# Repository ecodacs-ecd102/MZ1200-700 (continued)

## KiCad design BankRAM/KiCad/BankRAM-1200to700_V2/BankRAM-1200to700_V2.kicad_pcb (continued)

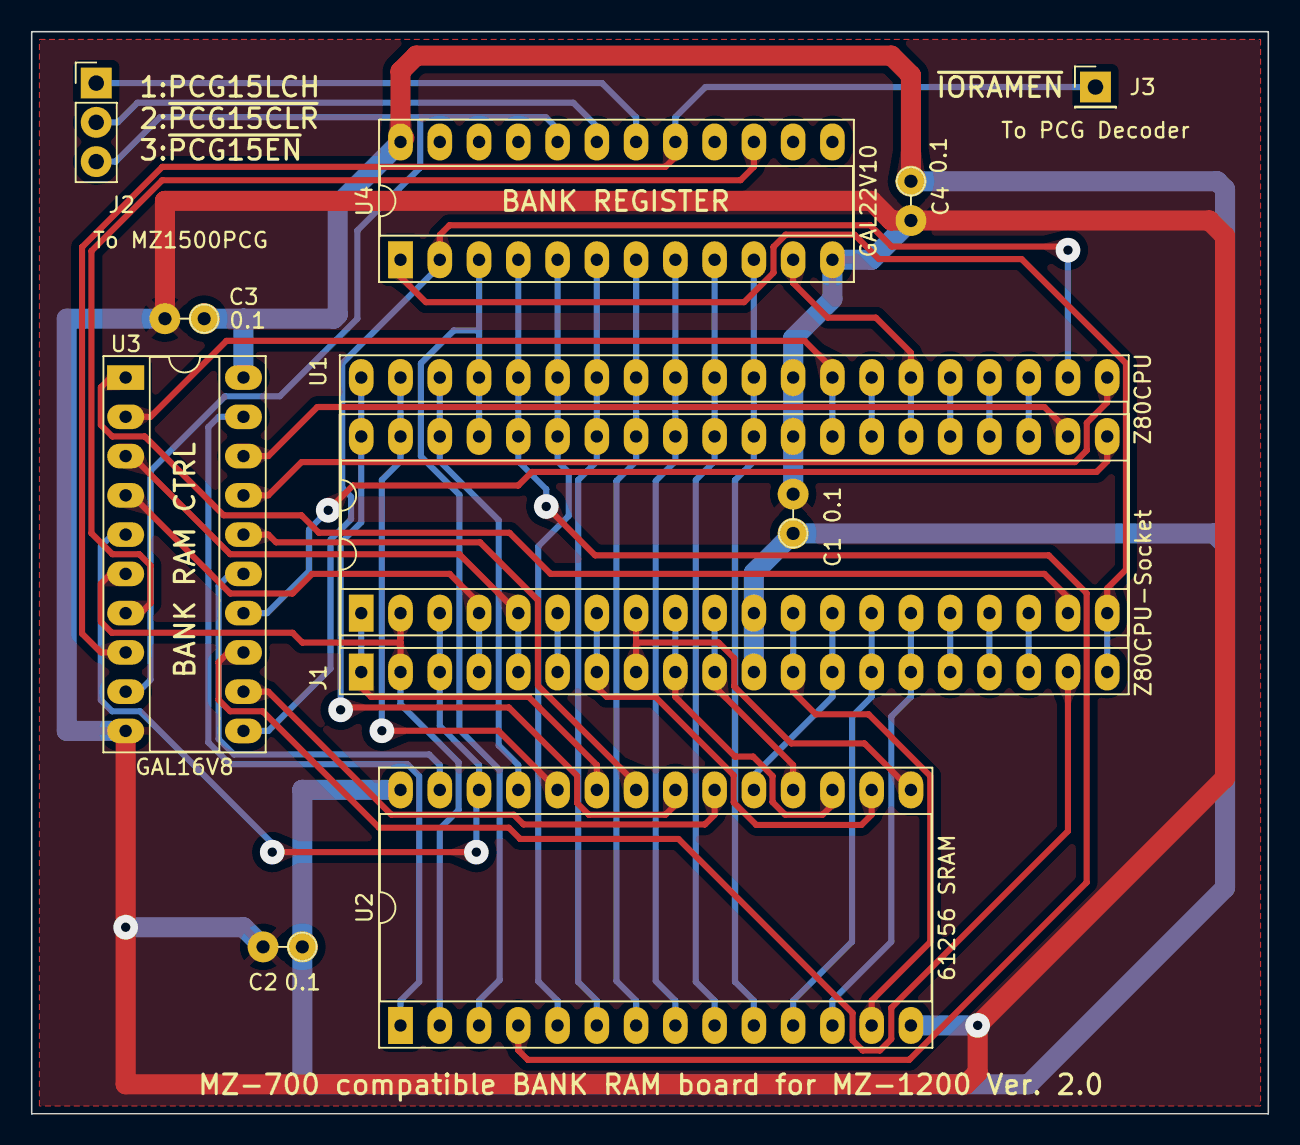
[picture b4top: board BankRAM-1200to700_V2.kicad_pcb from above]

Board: 2 copper layers, 80.0 x 70.0 mm, 11 parts (0 on the bottom side), 52 nets.

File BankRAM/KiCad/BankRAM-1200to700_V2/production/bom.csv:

Designator,Footprint,Quantity,Value,LCSC Part #
"C1, C2, C3, C4",LargePad_R_Axial_DIN0204_L3.6mm_D1.6mm_P2.54mm_Vertical,4,0.1,
J1,DIP-40_W15.24mm_Socket_LongPads,1,Z80CPU-Socket,
J2,PinHeader_1x03_P2.54mm_Vertical,1,To MZ1500PCG,
J3,PinHeader_1x01_P2.54mm_Vertical,1,To PCG Decoder,
U1,DIP-40_W15.24mm_Socket_LongPads,1,Z80CPU,
U2,DIP-28_W15.24mm_Socket_LongPads,1,61256 SRAM,
U3,DIP-20_W7.62mm_Socket_LongPads,1,GAL16V8,
U4,DIP-24_W7.62mm_Socket_LongPads,1,GAL22V10,

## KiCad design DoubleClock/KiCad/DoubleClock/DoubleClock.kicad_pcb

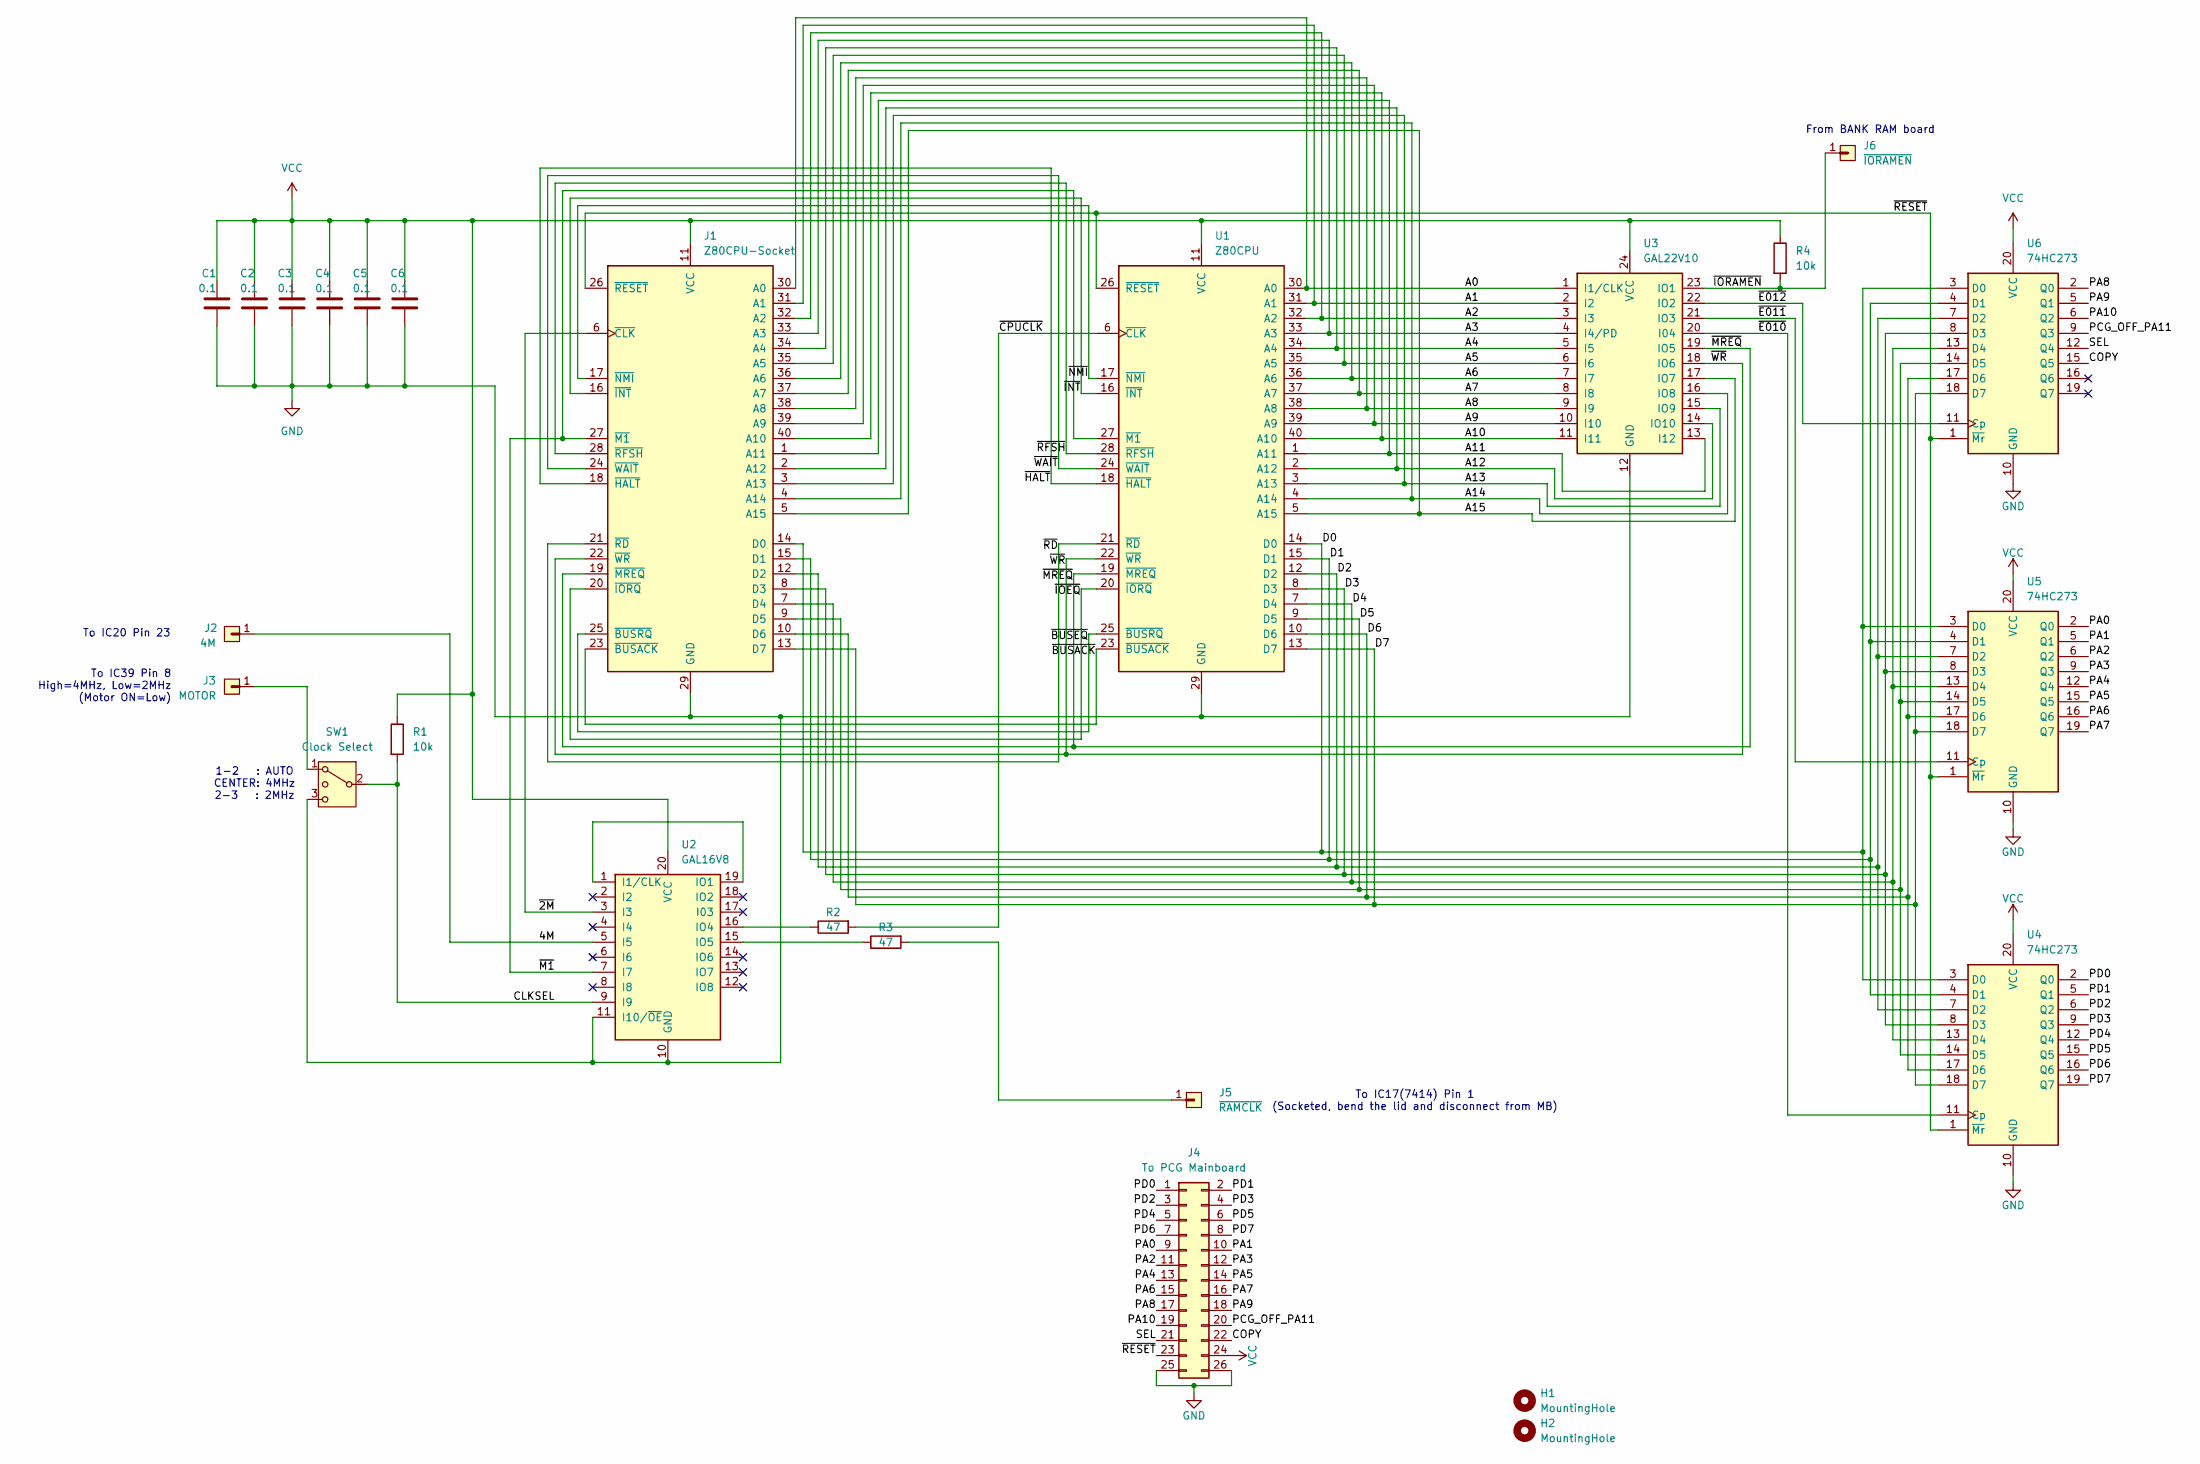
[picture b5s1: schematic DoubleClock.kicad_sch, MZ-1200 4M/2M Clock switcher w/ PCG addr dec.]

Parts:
C1, C2, C3, C4, C5, C6: 0.1; LargePad_R_Axial_DIN0207_L6.3mm_D2.5mm_P7.62mm_Horizontal
H1, H2: MountingHole; MountingHole_3.2mm_M3
J1: Z80CPU-Socket; DIP-40_W15.24mm_Socket_LongPads
J2: 4M; PinHeader_1x01_P2.54mm_Vertical
J3: MOTOR; PinHeader_1x01_P2.54mm_Vertical
J4: To PCG Mainboard; PinSocket_2x13_P2.54mm_Vertical_LargePad
J5: ~{RAMCLK}; PinHeader_1x01_P2.54mm_Vertical
J6: ~{IORAMEN}; PinHeader_1x01_P2.54mm_Vertical
R1, R4: 10k; LargePad_R_Axial_DIN0204_L3.6mm_D1.6mm_P2.54mm_Vertical
R2, R3: 47; LargePad_R_Axial_DIN0204_L3.6mm_D1.6mm_P2.54mm_Vertical
SW1: Clock Select; PinSocket_1x03_P2.54mm_Vertical
U1: Z80CPU; DIP-40_W15.24mm_Socket_LongPads
U2: GAL16V8; DIP-20_W7.62mm_Socket_LongPads
U3: GAL22V10; DIP-24_W7.62mm_Socket_LongPads
U4, U5, U6: 74HC273; DIP-20_W7.62mm_Socket_LongPads

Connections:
/4M: J2.1, U2.5 (I5)
/A0: J1.30 (A0), U1.30 (A0), U3.1 (I1/CLK)
/A1: J1.31 (A1), U1.31 (A1), U3.2 (I2)
/A2: J1.32 (A2), U1.32 (A2), U3.3 (I3)
/A3: J1.33 (A3), U1.33 (A3), U3.4 (I4/PD)
/A4: J1.34 (A4), U1.34 (A4), U3.5 (I5)
/A5: J1.35 (A5), U1.35 (A5), U3.6 (I6)
/A6: J1.36 (A6), U1.36 (A6), U3.7 (I7)
/A7: J1.37 (A7), U1.37 (A7), U3.8 (I8)
/A8: J1.38 (A8), U1.38 (A8), U3.9 (I9)
/A9: J1.39 (A9), U1.39 (A9), U3.10 (I10)
/A10: J1.40 (A10), U1.40 (A10), U3.11 (I11)
/A11: J1.1 (A11), U1.1 (A11), U3.13 (I12)
/A12: J1.2 (A12), U1.2 (A12), U3.14 (IO10)
/A13: J1.3 (A13), U1.3 (A13), U3.15 (IO9)
/A14: J1.4 (A14), U1.4 (A14), U3.16 (IO8)
/A15: J1.5 (A15), U1.5 (A15), U3.17 (IO7)
/CLKSEL: R1.2, SW1.2 (3), U2.9 (I9)
/COPY: J4.22, U6.15 (Q5)
/D0: J1.14 (D0), U1.14 (D0), U4.3 (D0), U5.3 (D0), U6.3 (D0)
/D1: J1.15 (D1), U1.15 (D1), U4.4 (D1), U5.4 (D1), U6.4 (D1)
/D2: J1.12 (D2), U1.12 (D2), U4.7 (D2), U5.7 (D2), U6.7 (D2)
/D3: J1.8 (D3), U1.8 (D3), U4.8 (D3), U5.8 (D3), U6.8 (D3)
/D4: J1.7 (D4), U1.7 (D4), U4.13 (D4), U5.13 (D4), U6.13 (D4)
/D5: J1.9 (D5), U1.9 (D5), U4.14 (D5), U5.14 (D5), U6.14 (D5)
/D6: J1.10 (D6), U1.10 (D6), U4.17 (D6), U5.17 (D6), U6.17 (D6)
/D7: J1.13 (D7), U1.13 (D7), U4.18 (D7), U5.18 (D7), U6.18 (D7)
/PA0: J4.9, U5.2 (Q0)
/PA1: J4.10, U5.5 (Q1)
/PA2: J4.11, U5.6 (Q2)
/PA3: J4.12, U5.9 (Q3)
/PA4: J4.13, U5.12 (Q4)
/PA5: J4.14, U5.15 (Q5)
/PA6: J4.15, U5.16 (Q6)
/PA7: J4.16, U5.19 (Q7)
/PA8: J4.17, U6.2 (Q0)
/PA9: J4.18, U6.5 (Q1)
/PA10: J4.19, U6.6 (Q2)
/PCG_OFF_PA11: J4.20, U6.9 (Q3)
/PD0: J4.1, U4.2 (Q0)
/PD1: J4.2, U4.5 (Q1)
/PD2: J4.3, U4.6 (Q2)
/PD3: J4.4, U4.9 (Q3)
/PD4: J4.5, U4.12 (Q4)
/PD5: J4.6, U4.15 (Q5)
/PD6: J4.7, U4.16 (Q6)
/PD7: J4.8, U4.19 (Q7)
/SEL: J4.21, U6.12 (Q4)
/~2M: J1.6 (~CLK), U2.3 (I3)
/~BUSACK: J1.23 (~BUSACK), U1.23 (~BUSACK)
/~BUSEQ: J1.25 (~BUSRQ), U1.25 (~BUSRQ)
/~CPUCLK: R2.2, U1.6 (~CLK)
/~E010: U3.20 (I04), U4.11 (Cp)
/~E011: U3.21 (IO3), U5.11 (Cp)
/~E012: U3.22 (IO2), U6.11 (Cp)
/~HALT: J1.18 (~HALT), U1.18 (~HALT)
/~INT: J1.16 (~INT), U1.16 (~INT)
/~IOEQ: J1.20 (~IORQ), U1.20 (~IORQ)
/~IORAMEN: J6.1, R4.2, U3.23 (IO1)
/~M1: J1.27 (~M1), U1.27 (~M1), U2.7 (I7)
/~MREQ: J1.19 (~MREQ), U1.19 (~MREQ), U3.19 (IO5)
/~NMI: J1.17 (~NMI), U1.17 (~NMI)
/~RD: J1.21 (~RD), U1.21 (~RD)
/~RESET: J1.26 (~RESET), J4.23, U1.26 (~RESET), U4.1 (~Mr), U5.1 (~Mr), U6.1 (~Mr)
/~RFSH: J1.28 (~RFSH), U1.28 (~RFSH)
/~WAIT: J1.24 (~WAIT), U1.24 (~WAIT)
/~WR: J1.22 (~WR), U1.22 (~WR), U3.18 (IO6)
GND: C1.2, C2.2, C3.2, C4.2, C5.2, C6.2, J1.29 (GND), J4.25, J4.26, SW1.3 (4), U1.29 (GND), U2.10 (GND), U2.11 (I10/~OE), U3.12 (GND), U4.10 (GND), U5.10 (GND), U6.10 (GND)
unnamed: J3.1, SW1.1
unnamed: J5.1, R3.2
unnamed: U2.1 (I1/CLK), U2.19 (IO1)
unnamed: R2.1, U2.16 (IO4)
unnamed: R3.1, U2.15 (IO5)
VCC: C1.1, C2.1, C3.1, C4.1, C5.1, C6.1, J1.11 (VCC), J4.24, R1.1, R4.1, U1.11 (VCC), U2.20 (VCC), U3.24 (VCC), U4.20 (VCC), U5.20 (VCC), U6.20 (VCC)

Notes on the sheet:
To IC17(7414) Pin 1 (Socketed, bend the lid and disconnect from MB)
1-2 : AUTO CENTER: 4MHz 2-3 : 2MHz
From BANK RAM board
To IC39 Pin 8 High=4MHz, Low=2MHz (Motor ON=Low)
To IC20 Pin 23

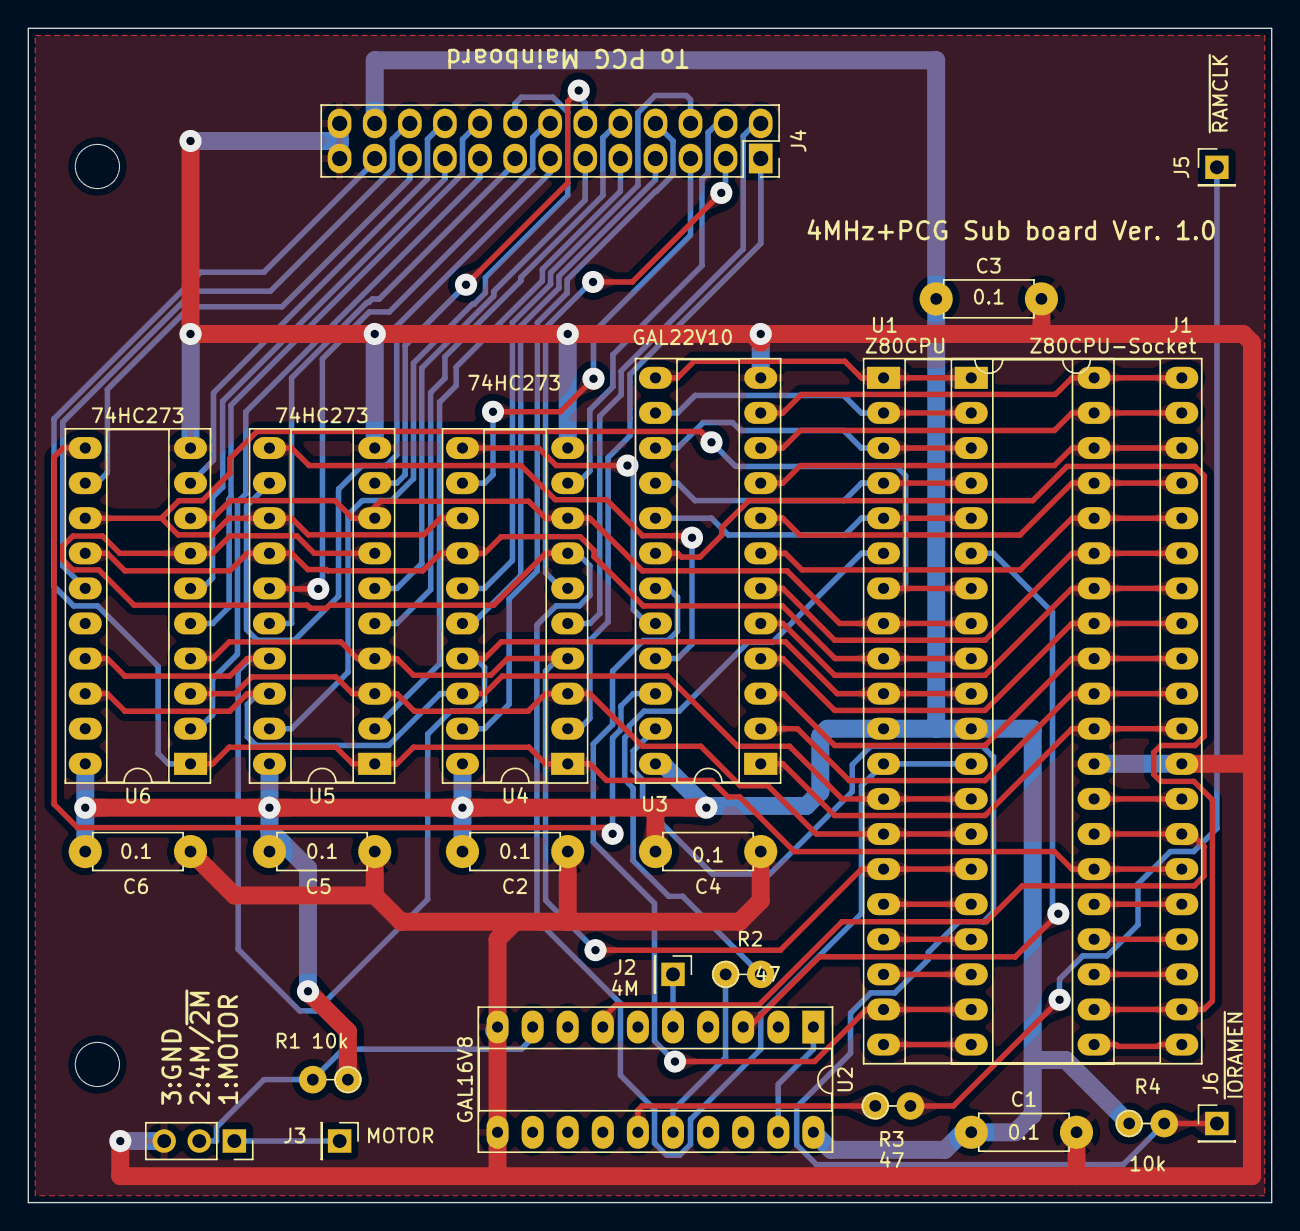
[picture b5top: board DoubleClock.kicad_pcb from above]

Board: 2 copper layers, 90.0 x 85.0 mm, 25 parts (0 on the bottom side), 74 nets.

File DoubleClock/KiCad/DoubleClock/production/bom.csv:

Designator,Footprint,Quantity,Value,LCSC Part #
"C1, C2, C3, C4, C5, C6",LargePad_R_Axial_DIN0207_L6.3mm_D2.5mm_P7.62mm_Horizontal,6,0.1,
"H1, H2",MountingHole_3.2mm_M3,2,MountingHole,
J1,DIP-40_W15.24mm_Socket_LongPads,1,Z80CPU-Socket,
J2,PinHeader_1x01_P2.54mm_Vertical,1,4M,
J3,PinHeader_1x01_P2.54mm_Vertical,1,MOTOR,
J4,PinSocket_2x13_P2.54mm_Vertical_LargePad,1,To PCG Mainboard,
J5,PinHeader_1x01_P2.54mm_Vertical,1,~{RAMCLK},
J6,PinHeader_1x01_P2.54mm_Vertical,1,~{IORAMEN},
"R1, R4",LargePad_R_Axial_DIN0204_L3.6mm_D1.6mm_P2.54mm_Vertical,2,10k,
"R2, R3",LargePad_R_Axial_DIN0204_L3.6mm_D1.6mm_P2.54mm_Vertical,2,47,
SW1,PinSocket_1x03_P2.54mm_Vertical,1,Clock Select,
U1,DIP-40_W15.24mm_Socket_LongPads,1,Z80CPU,
U2,DIP-20_W7.62mm_Socket_LongPads,1,GAL16V8,
U3,DIP-24_W7.62mm_Socket_LongPads,1,GAL22V10,
"U4, U5, U6",DIP-20_W7.62mm_Socket_LongPads,3,74HC273,

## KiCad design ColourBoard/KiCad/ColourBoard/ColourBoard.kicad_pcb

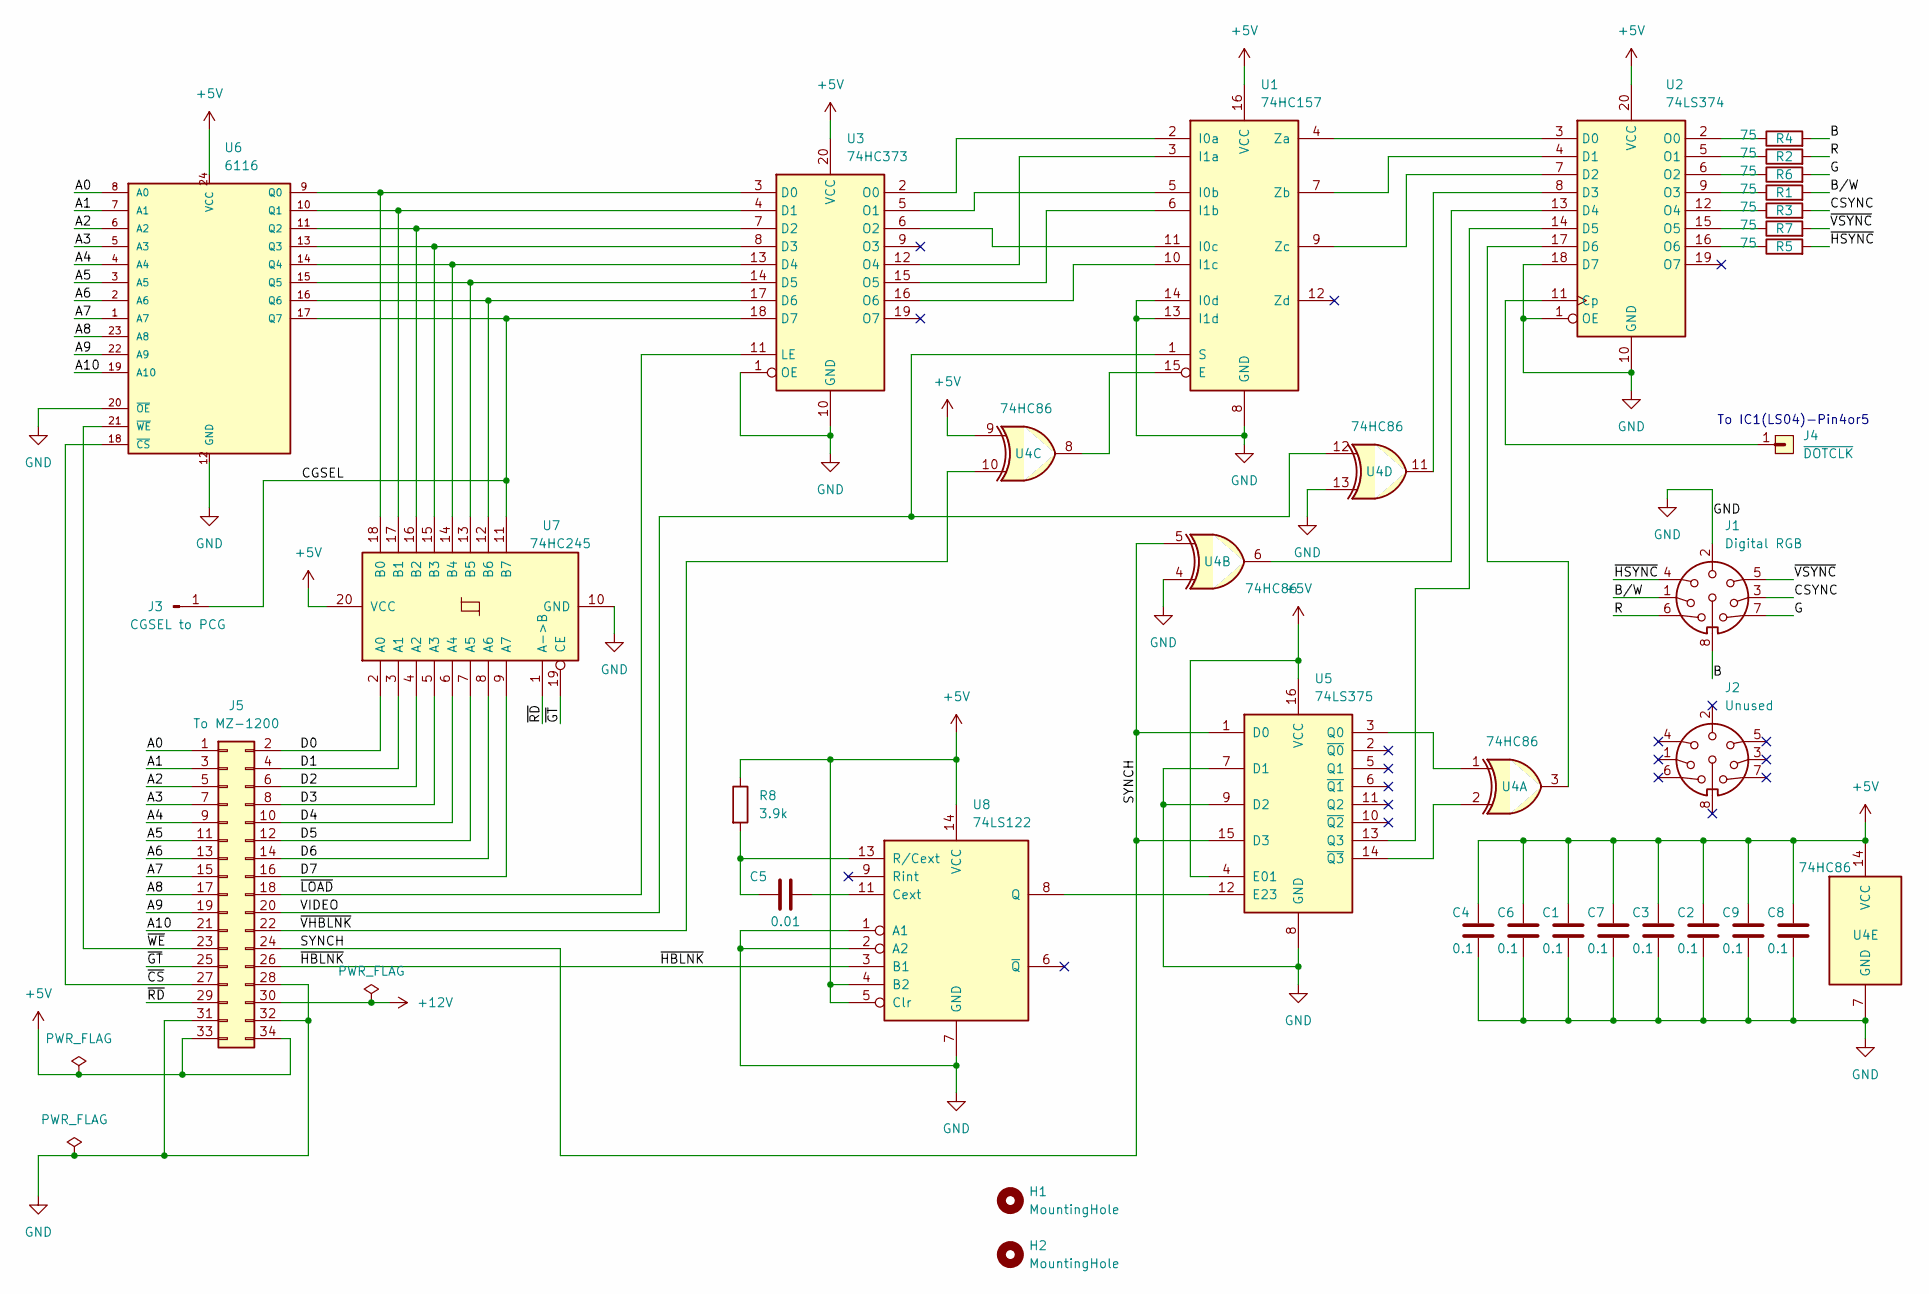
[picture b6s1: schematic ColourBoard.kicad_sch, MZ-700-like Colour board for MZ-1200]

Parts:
C1, C2, C3, C4, C6, C7, C8, C9: 0.1; LargePad_R_Axial_DIN0204_L3.6mm_D1.6mm_P2.54mm_Vertical
C5: 0.01; LargePad_R_Axial_DIN0204_L3.6mm_D1.6mm_P2.54mm_Vertical
H1, H2: MountingHole; MountingHole_4mm
J1: Digital RGB; DIN8P-2
J2: Unused; DIN8P-2
J3: CGSEL to PCG; PinHeader_1x01_P2.54mm_Vertical
J4: ~{DOTCLK}; PinHeader_1x01_P2.54mm_Vertical
J5: To MZ-1200; PinHeader_2x17_P2.54mm_Vertical
R1, R2, R3, R4, R5, R6, R7: 75; LargePad_R_Axial_DIN0204_L3.6mm_D1.6mm_P2.54mm_Vertical
R8: 3.9k; LargePad_R_Axial_DIN0204_L3.6mm_D1.6mm_P2.54mm_Vertical
U1: 74HC157; DIP-16_W7.62mm_Socket_LongPads
U2: 74LS374; DIP-20_W7.62mm_Socket_LongPads
U3: 74HC373; DIP-20_W7.62mm_Socket_LongPads
U4: 74HC86; DIP-14_W7.62mm_Socket_LongPads
U5: 74LS375; DIP-16_W7.62mm_Socket_LongPads
U6: 6116; DIP-24_W15.24mm_Socket_LongPads
U7: 74HC245; DIP-20_W7.62mm_Socket_LongPads
U8: 74LS122; DIP-14_W7.62mm_Socket_LongPads

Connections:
+5V: C1.1, C2.1, C3.1, C4.1, C6.1, C7.1, C8.1, C9.1, J5.33, J5.34, R8.1, U1.16 (VCC), U2.20 (VCC), U3.20 (VCC), U4.9, U4.14 (VCC), U5.4 (E01), U5.16 (VCC), U6.24 (VCC), U7.20 (VCC), U8.4 (B2), U8.5 (Clr), U8.14 (VCC)
+12V: J5.30
/A0: J5.1, U6.8 (A0)
/A1: J5.3, U6.7 (A1)
/A2: J5.5, U6.6 (A2)
/A3: J5.7, U6.5 (A3)
/A4: J5.9, U6.4 (A4)
/A5: J5.11, U6.3 (A5)
/A6: J5.13, U6.2 (A6)
/A7: J5.15, U6.1 (A7)
/A8: J5.17, U6.23 (A8)
/A9: J5.19, U6.22 (A9)
/A10: J5.21, U6.19 (A10)
/B: J1.8, R4.2
/B/W: J1.1, R1.2
/CGSEL: J3.1, U3.18 (D7), U6.17 (Q7), U7.11 (B7)
/CSYNC: J1.3, R3.2
/D0: J5.2, U7.2 (A0)
/D1: J5.4, U7.3 (A1)
/D2: J5.6, U7.4 (A2)
/D3: J5.8, U7.5 (A3)
/D4: J5.10, U7.6 (A4)
/D5: J5.12, U7.7 (A5)
/D6: J5.14, U7.8 (A6)
/D7: J5.16, U7.9 (A7)
/G: J1.7, R6.2
/R: J1.6, R2.2
/SYNCH: J5.24, U4.5, U5.1 (D0), U5.15 (D3)
/VIDEO: J5.20, U1.1 (S), U4.12
/~CS: J5.27, U6.18 (~CS)
/~GT: J5.25, U7.19 (CE)
/~HBLNK: J5.26, U8.3 (B1)
/~HSYNC: J1.4, R5.2
/~LOAD: J5.18, U3.11 (LE)
/~RD: J5.29, U7.1 (A->B)
/~VHBLNK: J5.22, U4.10
/~VSYNC: J1.5, R7.2
/~WE: J5.23, U6.21 (~WE)
GND: C1.2, C2.2, C3.2, C4.2, C6.2, C7.2, C8.2, C9.2, J1.2, J5.28, J5.31, J5.32, U1.8 (GND), U1.13 (I1d), U1.14 (I0d), U2.1 (OE), U2.10 (GND), U2.18 (D7), U3.1 (OE), U3.10 (GND), U4.4, U4.7 (GND), U4.13, U5.7 (D1), U5.8 (GND), U5.9 (D2), U6.12 (GND), U6.20 (~OE), U7.10 (GND), U8.1 (A1), U8.2 (A2), U8.7 (GND)
unnamed: U1.15 (E), U4.8
unnamed: U1.2 (I0a), U3.2 (O0)
unnamed: U1.5 (I0b), U3.5 (O1)
unnamed: U1.11 (I0c), U3.6 (O2)
unnamed: U1.3 (I1a), U3.12 (O4)
unnamed: U1.6 (I1b), U3.15 (O5)
unnamed: U1.10 (I1c), U3.16 (O6)
unnamed: U1.4 (Za), U2.3 (D0)
unnamed: U1.7 (Zb), U2.4 (D1)
unnamed: U1.9 (Zc), U2.7 (D2)
unnamed: J4.1, U2.11 (Cp)
unnamed: U2.8 (D3), U4.11
unnamed: U2.13 (D4), U4.6
unnamed: U2.14 (D5), U5.13 (Q3)
unnamed: U2.17 (D6), U4.3
unnamed: R4.1, U2.2 (O0)
unnamed: R2.1, U2.5 (O1)
unnamed: R6.1, U2.6 (O2)
unnamed: R1.1, U2.9 (O3)
unnamed: R3.1, U2.12 (O4)
unnamed: R7.1, U2.15 (O5)
unnamed: R5.1, U2.16 (O6)
unnamed: U3.3 (D0), U6.9 (Q0), U7.18 (B0)
unnamed: U3.4 (D1), U6.10 (Q1), U7.17 (B1)
unnamed: U3.7 (D2), U6.11 (Q2), U7.16 (B2)
unnamed: U3.8 (D3), U6.13 (Q3), U7.15 (B3)
unnamed: U3.13 (D4), U6.14 (Q4), U7.14 (B4)
unnamed: U3.14 (D5), U6.15 (Q5), U7.13 (B5)
unnamed: U3.17 (D6), U6.16 (Q6), U7.12 (B6)
unnamed: U5.12 (E23), U8.8 (Q)
unnamed: U4.1, U5.3 (Q0)
unnamed: U4.2, U5.14 (~Q3)
unnamed: C5.2, U8.11 (Cext), U8.12 (NC)
unnamed: C5.1, R8.2, U8.13 (R/Cext)

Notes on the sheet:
To IC1(LS04)-Pin4or5

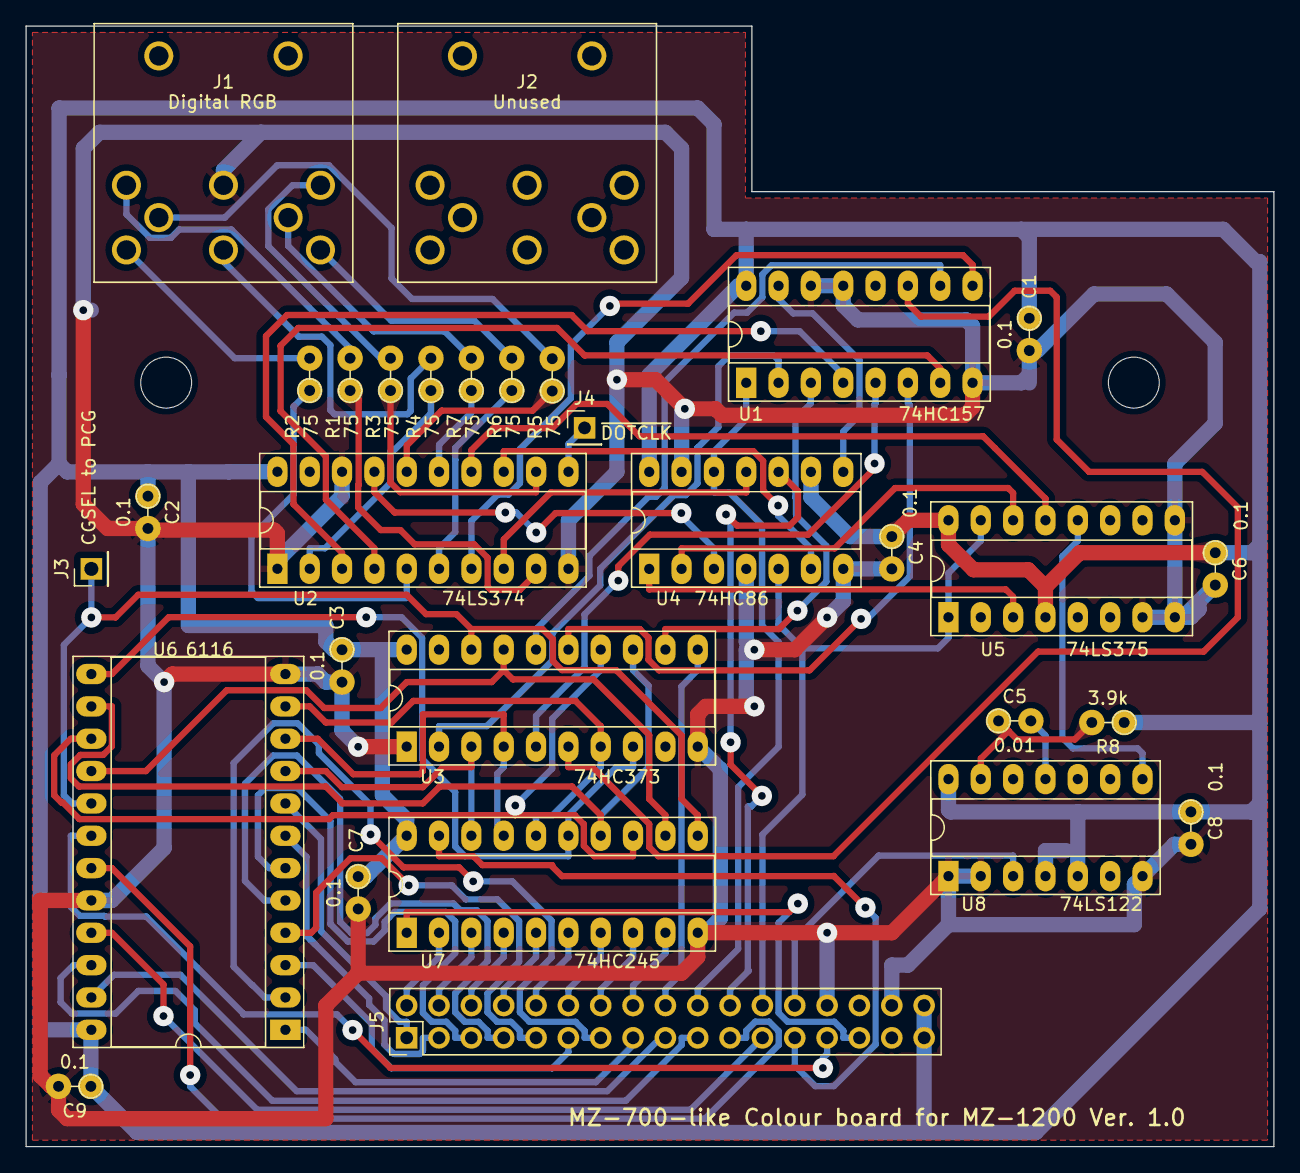
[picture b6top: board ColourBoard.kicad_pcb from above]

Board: 2 copper layers, 98.0 x 88.0 mm, 32 parts (0 on the bottom side), 72 nets.

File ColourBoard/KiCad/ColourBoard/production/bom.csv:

Designator,Footprint,Quantity,Value,LCSC Part #
"C1, C2, C3, C4, C6, C7, C8, C9",LargePad_R_Axial_DIN0204_L3.6mm_D1.6mm_P2.54mm_Vertical,8,0.1,
C5,LargePad_R_Axial_DIN0204_L3.6mm_D1.6mm_P2.54mm_Vertical,1,0.01,
"H1, H2",MountingHole_4mm,2,MountingHole,
J1,DIN8P-2,1,Digital RGB,
J2,DIN8P-2,1,Unused,
J3,PinHeader_1x01_P2.54mm_Vertical,1,CGSEL to PCG,
J4,PinHeader_1x01_P2.54mm_Vertical,1,~{DOTCLK},
J5,PinHeader_2x17_P2.54mm_Vertical,1,To MZ-1200,
"R1, R2, R3, R4, R5, R6, R7",LargePad_R_Axial_DIN0204_L3.6mm_D1.6mm_P2.54mm_Vertical,7,75,
R8,LargePad_R_Axial_DIN0204_L3.6mm_D1.6mm_P2.54mm_Vertical,1,3.9k,
U1,DIP-16_W7.62mm_Socket_LongPads,1,74HC157,
U2,DIP-20_W7.62mm_Socket_LongPads,1,74LS374,
U3,DIP-20_W7.62mm_Socket_LongPads,1,74HC373,
U4,DIP-14_W7.62mm_Socket_LongPads,1,74HC86,
U5,DIP-16_W7.62mm_Socket_LongPads,1,74LS375,
U6,DIP-24_W15.24mm_Socket_LongPads,1,6116,
U7,DIP-20_W7.62mm_Socket_LongPads,1,74HC245,
U8,DIP-14_W7.62mm_Socket_LongPads,1,74LS122,
